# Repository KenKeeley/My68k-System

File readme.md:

# My Motorola 680x0 home built computer system.

My68k System is a home built Motorola 680x0 based small computer project. It is made in the style of vintage computers of the mid
to late 1970's and early 1980's using a mix of classic and modern technologies. The My68k System is made up of multiple PCB's
connected via a common back plane that is loosely based on the VMEBus standard.

The purpose of the My68k System is to entertain through education. It is intended to be used to teach and promote principles of
electronic computer design. It is a solely non-profit educational project and is not intended for any commercial application.
The My68k System and related peripherals would be ideal as a small project to teach basic computer hardware and software
principles.

#### SOFTWARE USED
- [FreeCAD](https://www.freecadweb.org/)
- [KiCad](http://kicad-pcb.org/)
- [KiCad StepUp](https://kicadstepup.sourceforge.io/)

Please report any issues and/or bugs via the "Issues" section on github.
If you have any extra reference material then please submit it via the "Issues" section on github.

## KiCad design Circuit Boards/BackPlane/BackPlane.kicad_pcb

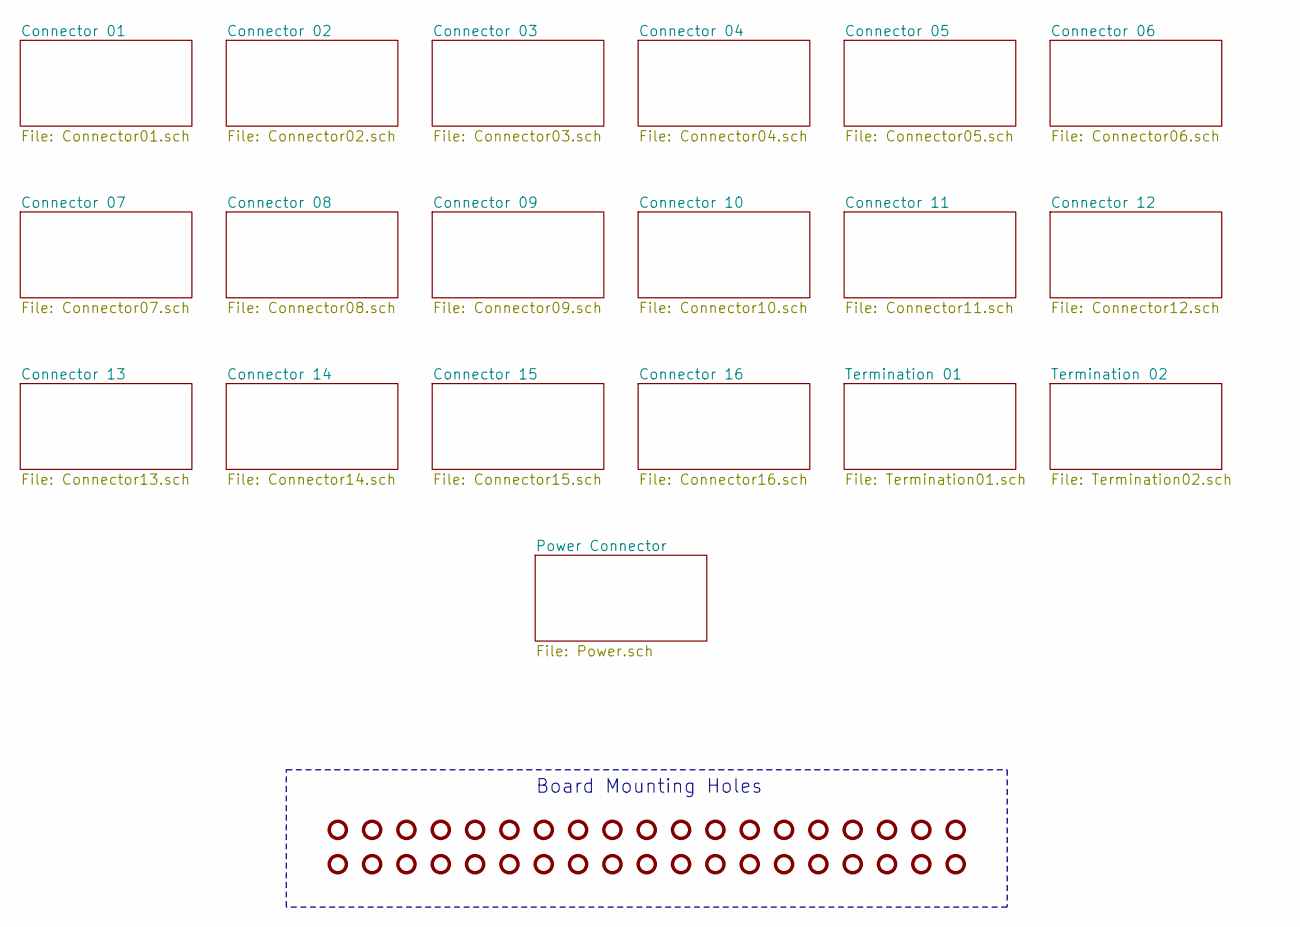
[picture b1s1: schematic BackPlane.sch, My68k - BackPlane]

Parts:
MH1: BackPlane Rails; BackPlane_Rails

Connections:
GND: MH1.1, MH1.2, MH1.3, MH1.4, MH1.5, MH1.6, MH1.7, MH1.8, MH1.9, MH1.10, MH1.11, MH1.12, MH1.13, MH1.14, MH1.15, MH1.16, MH1.17, MH1.18, MH1.19, MH1.20, MH1.21, MH1.22, MH1.23, MH1.24, MH1.25, MH1.26, MH1.27, MH1.28, MH1.29, MH1.30, MH1.31, MH1.32, MH1.33, MH1.34, MH1.35, MH1.36, MH1.37, MH1.38; also elsewhere on the board

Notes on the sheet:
Board Mounting Holes

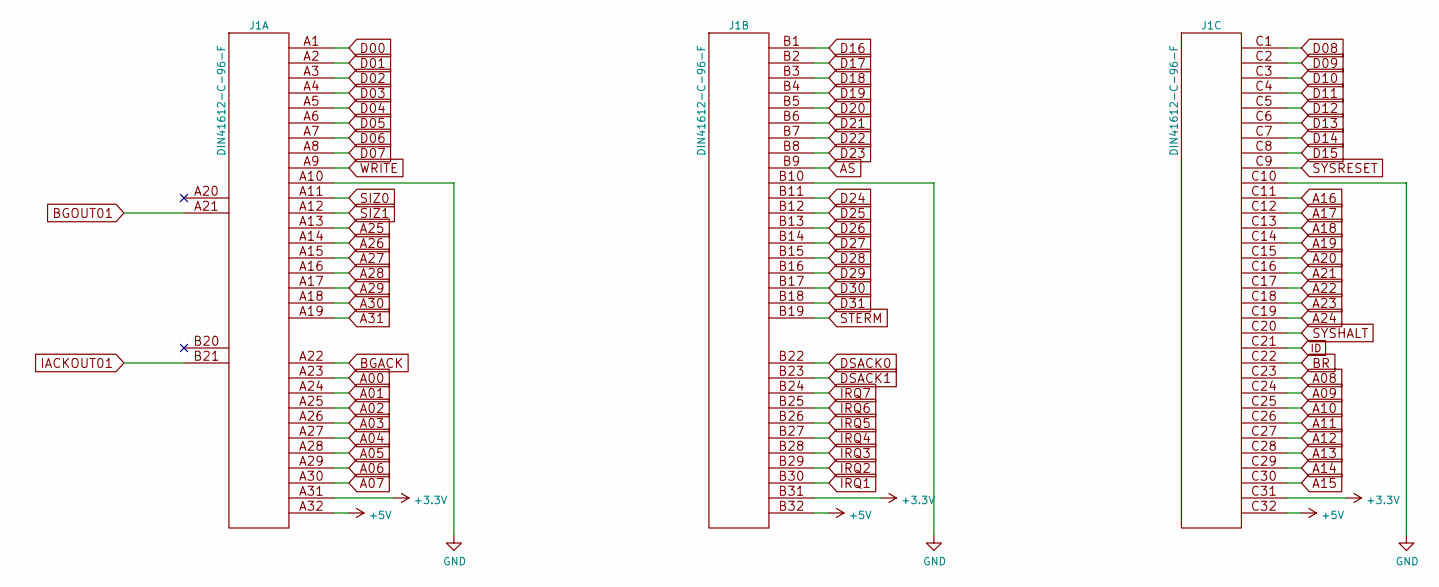
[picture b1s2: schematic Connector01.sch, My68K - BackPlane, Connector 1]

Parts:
J1: DIN41612-C-96-F; Part No. 1656359

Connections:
+3V3: J1.A31, J1.B31, J1.C31; also elsewhere on the board
+5V: J1.A32, J1.B32, J1.C32; also elsewhere on the board
A00: J1.A23; also elsewhere on the board
A01: J1.A24; also elsewhere on the board
A02: J1.A25; also elsewhere on the board
A03: J1.A26; also elsewhere on the board
A04: J1.A27; also elsewhere on the board
A05: J1.A28; also elsewhere on the board
A06: J1.A29; also elsewhere on the board
A07: J1.A30; also elsewhere on the board
A08: J1.C23; also elsewhere on the board
A09: J1.C24; also elsewhere on the board
A10: J1.C25; also elsewhere on the board
A11: J1.C26; also elsewhere on the board
A12: J1.C27; also elsewhere on the board
A13: J1.C28; also elsewhere on the board
A14: J1.C29; also elsewhere on the board
A15: J1.C30; also elsewhere on the board
A16: J1.C11; also elsewhere on the board
A17: J1.C12; also elsewhere on the board
A18: J1.C13; also elsewhere on the board
A19: J1.C14; also elsewhere on the board
A20: J1.C15; also elsewhere on the board
A21: J1.C16; also elsewhere on the board
A22: J1.C17; also elsewhere on the board
A23: J1.C18; also elsewhere on the board
A24: J1.C19; also elsewhere on the board
A25: J1.A13; also elsewhere on the board
A26: J1.A14; also elsewhere on the board
A27: J1.A15; also elsewhere on the board
A28: J1.A16; also elsewhere on the board
A29: J1.A17; also elsewhere on the board
A30: J1.A18; also elsewhere on the board
A31: J1.A19; also elsewhere on the board
AS: J1.B9; also elsewhere on the board
BGACK: J1.A22; also elsewhere on the board
BGOUT01: J1.A21; also elsewhere on the board
BR: J1.C22; also elsewhere on the board
D00: J1.A1; also elsewhere on the board
D01: J1.A2; also elsewhere on the board
D02: J1.A3; also elsewhere on the board
D03: J1.A4; also elsewhere on the board
D04: J1.A5; also elsewhere on the board
D05: J1.A6; also elsewhere on the board
D06: J1.A7; also elsewhere on the board
D07: J1.A8; also elsewhere on the board
D08: J1.C1; also elsewhere on the board
D09: J1.C2; also elsewhere on the board
D10: J1.C3; also elsewhere on the board
D11: J1.C4; also elsewhere on the board
D12: J1.C5; also elsewhere on the board
D13: J1.C6; also elsewhere on the board
D14: J1.C7; also elsewhere on the board
D15: J1.C8; also elsewhere on the board
D16: J1.B1; also elsewhere on the board
D17: J1.B2; also elsewhere on the board
D18: J1.B3; also elsewhere on the board
D19: J1.B4; also elsewhere on the board
D20: J1.B5; also elsewhere on the board
D21: J1.B6; also elsewhere on the board
D22: J1.B7; also elsewhere on the board
D23: J1.B8; also elsewhere on the board
D24: J1.B11; also elsewhere on the board
D25: J1.B12; also elsewhere on the board
D26: J1.B13; also elsewhere on the board
D27: J1.B14; also elsewhere on the board
D28: J1.B15; also elsewhere on the board
D29: J1.B16; also elsewhere on the board
D30: J1.B17; also elsewhere on the board
D31: J1.B18; also elsewhere on the board
DSACK0: J1.B22; also elsewhere on the board
DSACK1: J1.B23; also elsewhere on the board
GND: J1.33 (GND), J1.34 (GND), J1.A10, J1.B10, J1.C10; also elsewhere on the board
IACKOUT01: J1.B21; also elsewhere on the board
ID: J1.C21; also elsewhere on the board
IRQ1: J1.B30; also elsewhere on the board
IRQ2: J1.B29; also elsewhere on the board
IRQ3: J1.B28; also elsewhere on the board
IRQ4: J1.B27; also elsewhere on the board
IRQ5: J1.B26; also elsewhere on the board
IRQ6: J1.B25; also elsewhere on the board
IRQ7: J1.B24; also elsewhere on the board
SIZ0: J1.A11; also elsewhere on the board
SIZ1: J1.A12; also elsewhere on the board
STERM: J1.B19; also elsewhere on the board
SYSHALT: J1.C20; also elsewhere on the board
SYSRESET: J1.C9; also elsewhere on the board
WRITE: J1.A9; also elsewhere on the board

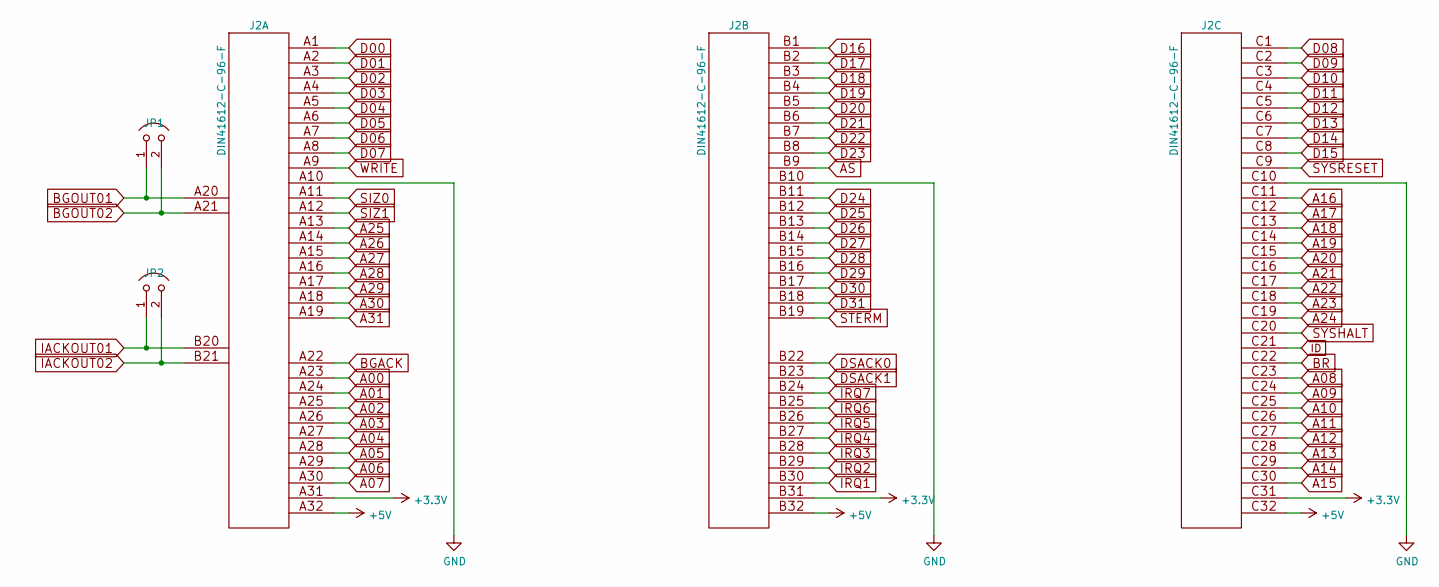
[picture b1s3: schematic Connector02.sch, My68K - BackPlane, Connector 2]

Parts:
J2: DIN41612-C-96-F; Part No. 1656359
JP1, JP2: Jumper; Part No. 1593411

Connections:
+3V3: J2.A31, J2.B31, J2.C31; also elsewhere on the board
+5V: J2.A32, J2.B32, J2.C32; also elsewhere on the board
A00: J2.A23; also elsewhere on the board
A01: J2.A24; also elsewhere on the board
A02: J2.A25; also elsewhere on the board
A03: J2.A26; also elsewhere on the board
A04: J2.A27; also elsewhere on the board
A05: J2.A28; also elsewhere on the board
A06: J2.A29; also elsewhere on the board
A07: J2.A30; also elsewhere on the board
A08: J2.C23; also elsewhere on the board
A09: J2.C24; also elsewhere on the board
A10: J2.C25; also elsewhere on the board
A11: J2.C26; also elsewhere on the board
A12: J2.C27; also elsewhere on the board
A13: J2.C28; also elsewhere on the board
A14: J2.C29; also elsewhere on the board
A15: J2.C30; also elsewhere on the board
A16: J2.C11; also elsewhere on the board
A17: J2.C12; also elsewhere on the board
A18: J2.C13; also elsewhere on the board
A19: J2.C14; also elsewhere on the board
A20: J2.C15; also elsewhere on the board
A21: J2.C16; also elsewhere on the board
A22: J2.C17; also elsewhere on the board
A23: J2.C18; also elsewhere on the board
A24: J2.C19; also elsewhere on the board
A25: J2.A13; also elsewhere on the board
A26: J2.A14; also elsewhere on the board
A27: J2.A15; also elsewhere on the board
A28: J2.A16; also elsewhere on the board
A29: J2.A17; also elsewhere on the board
A30: J2.A18; also elsewhere on the board
A31: J2.A19; also elsewhere on the board
AS: J2.B9; also elsewhere on the board
BGACK: J2.A22; also elsewhere on the board
BGOUT01: J2.A20, JP1.1; also elsewhere on the board
BGOUT02: J2.A21, JP1.2; also elsewhere on the board
BR: J2.C22; also elsewhere on the board
D00: J2.A1; also elsewhere on the board
D01: J2.A2; also elsewhere on the board
D02: J2.A3; also elsewhere on the board
D03: J2.A4; also elsewhere on the board
D04: J2.A5; also elsewhere on the board
D05: J2.A6; also elsewhere on the board
D06: J2.A7; also elsewhere on the board
D07: J2.A8; also elsewhere on the board
D08: J2.C1; also elsewhere on the board
D09: J2.C2; also elsewhere on the board
D10: J2.C3; also elsewhere on the board
D11: J2.C4; also elsewhere on the board
D12: J2.C5; also elsewhere on the board
D13: J2.C6; also elsewhere on the board
D14: J2.C7; also elsewhere on the board
D15: J2.C8; also elsewhere on the board
D16: J2.B1; also elsewhere on the board
D17: J2.B2; also elsewhere on the board
D18: J2.B3; also elsewhere on the board
D19: J2.B4; also elsewhere on the board
D20: J2.B5; also elsewhere on the board
D21: J2.B6; also elsewhere on the board
D22: J2.B7; also elsewhere on the board
D23: J2.B8; also elsewhere on the board
D24: J2.B11; also elsewhere on the board
D25: J2.B12; also elsewhere on the board
D26: J2.B13; also elsewhere on the board
D27: J2.B14; also elsewhere on the board
D28: J2.B15; also elsewhere on the board
D29: J2.B16; also elsewhere on the board
D30: J2.B17; also elsewhere on the board
D31: J2.B18; also elsewhere on the board
DSACK0: J2.B22; also elsewhere on the board
DSACK1: J2.B23; also elsewhere on the board
GND: J2.33 (GND), J2.34 (GND), J2.A10, J2.B10, J2.C10; also elsewhere on the board
IACKOUT01: J2.B20, JP2.1; also elsewhere on the board
IACKOUT02: J2.B21, JP2.2; also elsewhere on the board
ID: J2.C21; also elsewhere on the board
IRQ1: J2.B30; also elsewhere on the board
IRQ2: J2.B29; also elsewhere on the board
IRQ3: J2.B28; also elsewhere on the board
IRQ4: J2.B27; also elsewhere on the board
IRQ5: J2.B26; also elsewhere on the board
IRQ6: J2.B25; also elsewhere on the board
IRQ7: J2.B24; also elsewhere on the board
SIZ0: J2.A11; also elsewhere on the board
SIZ1: J2.A12; also elsewhere on the board
STERM: J2.B19; also elsewhere on the board
SYSHALT: J2.C20; also elsewhere on the board
SYSRESET: J2.C9; also elsewhere on the board
WRITE: J2.A9; also elsewhere on the board

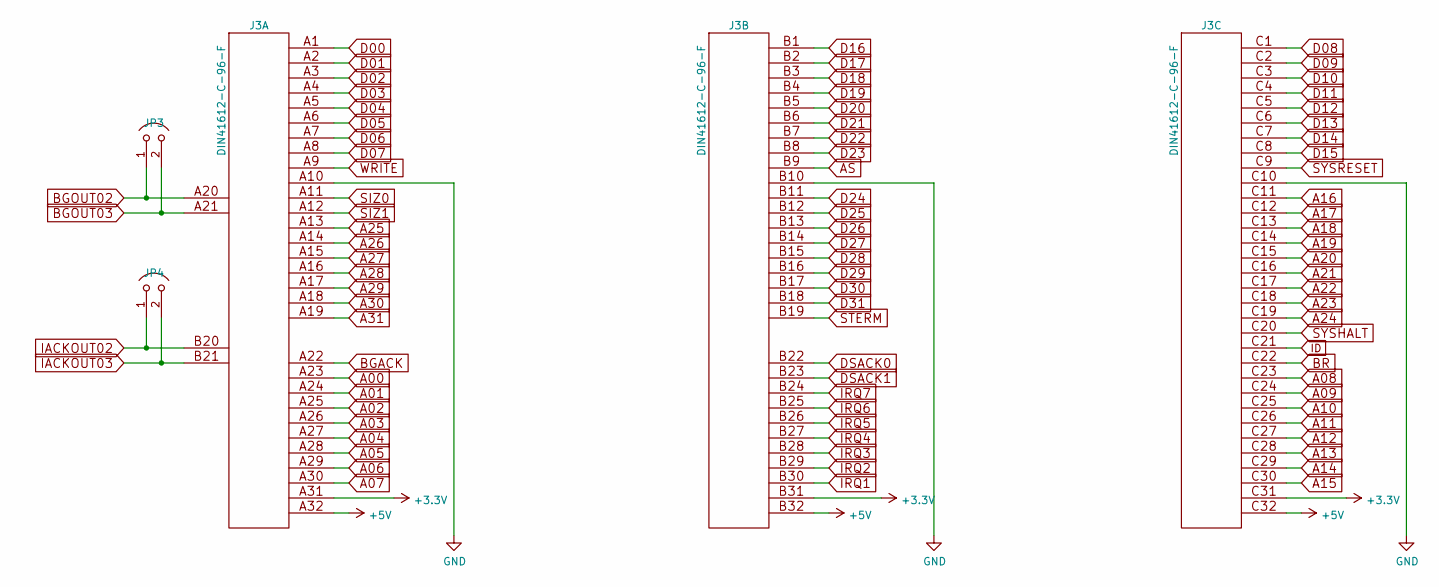
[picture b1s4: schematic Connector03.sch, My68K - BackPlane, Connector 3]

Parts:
J3: DIN41612-C-96-F; Part No. 1656359
JP3, JP4: Jumper; Part No. 1593411

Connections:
+3V3: J3.A31, J3.B31, J3.C31; also elsewhere on the board
+5V: J3.A32, J3.B32, J3.C32; also elsewhere on the board
A00: J3.A23; also elsewhere on the board
A01: J3.A24; also elsewhere on the board
A02: J3.A25; also elsewhere on the board
A03: J3.A26; also elsewhere on the board
A04: J3.A27; also elsewhere on the board
A05: J3.A28; also elsewhere on the board
A06: J3.A29; also elsewhere on the board
A07: J3.A30; also elsewhere on the board
A08: J3.C23; also elsewhere on the board
A09: J3.C24; also elsewhere on the board
A10: J3.C25; also elsewhere on the board
A11: J3.C26; also elsewhere on the board
A12: J3.C27; also elsewhere on the board
A13: J3.C28; also elsewhere on the board
A14: J3.C29; also elsewhere on the board
A15: J3.C30; also elsewhere on the board
A16: J3.C11; also elsewhere on the board
A17: J3.C12; also elsewhere on the board
A18: J3.C13; also elsewhere on the board
A19: J3.C14; also elsewhere on the board
A20: J3.C15; also elsewhere on the board
A21: J3.C16; also elsewhere on the board
A22: J3.C17; also elsewhere on the board
A23: J3.C18; also elsewhere on the board
A24: J3.C19; also elsewhere on the board
A25: J3.A13; also elsewhere on the board
A26: J3.A14; also elsewhere on the board
A27: J3.A15; also elsewhere on the board
A28: J3.A16; also elsewhere on the board
A29: J3.A17; also elsewhere on the board
A30: J3.A18; also elsewhere on the board
A31: J3.A19; also elsewhere on the board
AS: J3.B9; also elsewhere on the board
BGACK: J3.A22; also elsewhere on the board
BGOUT02: J3.A20, JP3.1; also elsewhere on the board
BGOUT03: J3.A21, JP3.2; also elsewhere on the board
BR: J3.C22; also elsewhere on the board
D00: J3.A1; also elsewhere on the board
D01: J3.A2; also elsewhere on the board
D02: J3.A3; also elsewhere on the board
D03: J3.A4; also elsewhere on the board
D04: J3.A5; also elsewhere on the board
D05: J3.A6; also elsewhere on the board
D06: J3.A7; also elsewhere on the board
D07: J3.A8; also elsewhere on the board
D08: J3.C1; also elsewhere on the board
D09: J3.C2; also elsewhere on the board
D10: J3.C3; also elsewhere on the board
D11: J3.C4; also elsewhere on the board
D12: J3.C5; also elsewhere on the board
D13: J3.C6; also elsewhere on the board
D14: J3.C7; also elsewhere on the board
D15: J3.C8; also elsewhere on the board
D16: J3.B1; also elsewhere on the board
D17: J3.B2; also elsewhere on the board
D18: J3.B3; also elsewhere on the board
D19: J3.B4; also elsewhere on the board
D20: J3.B5; also elsewhere on the board
D21: J3.B6; also elsewhere on the board
D22: J3.B7; also elsewhere on the board
D23: J3.B8; also elsewhere on the board
D24: J3.B11; also elsewhere on the board
D25: J3.B12; also elsewhere on the board
D26: J3.B13; also elsewhere on the board
D27: J3.B14; also elsewhere on the board
D28: J3.B15; also elsewhere on the board
D29: J3.B16; also elsewhere on the board
D30: J3.B17; also elsewhere on the board
D31: J3.B18; also elsewhere on the board
DSACK0: J3.B22; also elsewhere on the board
DSACK1: J3.B23; also elsewhere on the board
GND: J3.33 (GND), J3.34 (GND), J3.A10, J3.B10, J3.C10; also elsewhere on the board
IACKOUT02: J3.B20, JP4.1; also elsewhere on the board
IACKOUT03: J3.B21, JP4.2; also elsewhere on the board
ID: J3.C21; also elsewhere on the board
IRQ1: J3.B30; also elsewhere on the board
IRQ2: J3.B29; also elsewhere on the board
IRQ3: J3.B28; also elsewhere on the board
IRQ4: J3.B27; also elsewhere on the board
IRQ5: J3.B26; also elsewhere on the board
IRQ6: J3.B25; also elsewhere on the board
IRQ7: J3.B24; also elsewhere on the board
SIZ0: J3.A11; also elsewhere on the board
SIZ1: J3.A12; also elsewhere on the board
STERM: J3.B19; also elsewhere on the board
SYSHALT: J3.C20; also elsewhere on the board
SYSRESET: J3.C9; also elsewhere on the board
WRITE: J3.A9; also elsewhere on the board

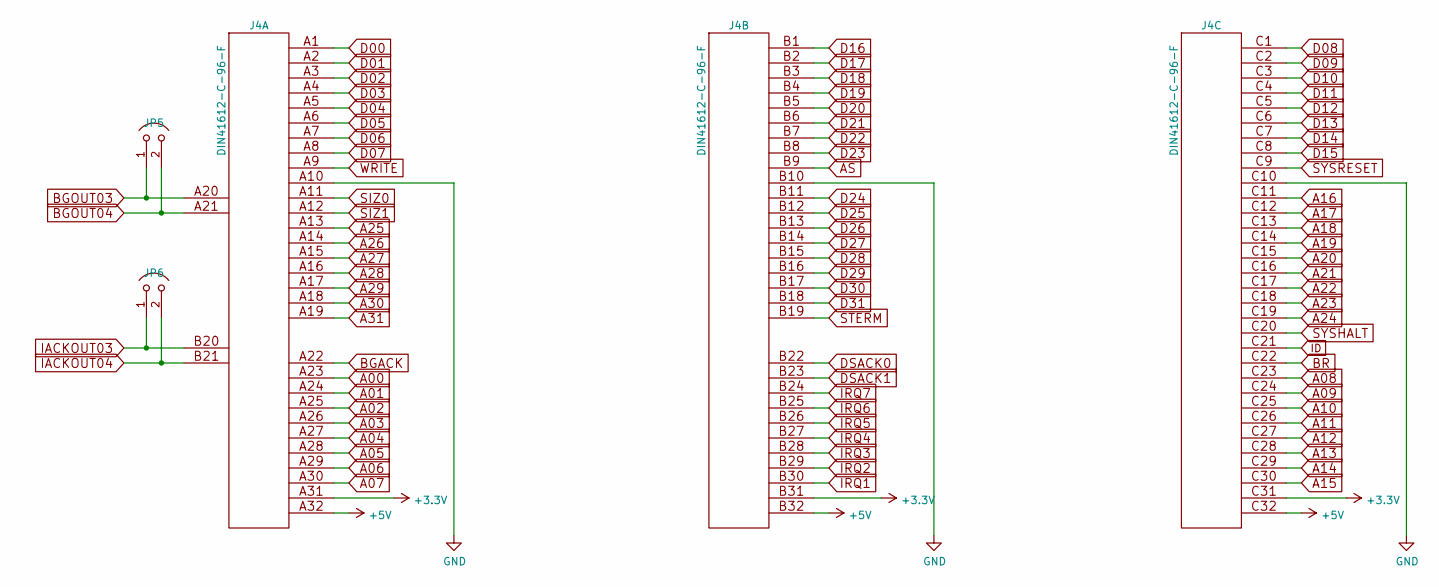
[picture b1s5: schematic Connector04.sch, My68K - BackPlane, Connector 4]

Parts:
J4: DIN41612-C-96-F; Part No. 1656359
JP5, JP6: Jumper; Part No. 1593411

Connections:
+3V3: J4.A31, J4.B31, J4.C31; also elsewhere on the board
+5V: J4.A32, J4.B32, J4.C32; also elsewhere on the board
A00: J4.A23; also elsewhere on the board
A01: J4.A24; also elsewhere on the board
A02: J4.A25; also elsewhere on the board
A03: J4.A26; also elsewhere on the board
A04: J4.A27; also elsewhere on the board
A05: J4.A28; also elsewhere on the board
A06: J4.A29; also elsewhere on the board
A07: J4.A30; also elsewhere on the board
A08: J4.C23; also elsewhere on the board
A09: J4.C24; also elsewhere on the board
A10: J4.C25; also elsewhere on the board
A11: J4.C26; also elsewhere on the board
A12: J4.C27; also elsewhere on the board
A13: J4.C28; also elsewhere on the board
A14: J4.C29; also elsewhere on the board
A15: J4.C30; also elsewhere on the board
A16: J4.C11; also elsewhere on the board
A17: J4.C12; also elsewhere on the board
A18: J4.C13; also elsewhere on the board
A19: J4.C14; also elsewhere on the board
A20: J4.C15; also elsewhere on the board
A21: J4.C16; also elsewhere on the board
A22: J4.C17; also elsewhere on the board
A23: J4.C18; also elsewhere on the board
A24: J4.C19; also elsewhere on the board
A25: J4.A13; also elsewhere on the board
A26: J4.A14; also elsewhere on the board
A27: J4.A15; also elsewhere on the board
A28: J4.A16; also elsewhere on the board
A29: J4.A17; also elsewhere on the board
A30: J4.A18; also elsewhere on the board
A31: J4.A19; also elsewhere on the board
AS: J4.B9; also elsewhere on the board
BGACK: J4.A22; also elsewhere on the board
BGOUT03: J4.A20, JP5.1; also elsewhere on the board
BGOUT04: J4.A21, JP5.2; also elsewhere on the board
BR: J4.C22; also elsewhere on the board
D00: J4.A1; also elsewhere on the board
D01: J4.A2; also elsewhere on the board
D02: J4.A3; also elsewhere on the board
D03: J4.A4; also elsewhere on the board
D04: J4.A5; also elsewhere on the board
D05: J4.A6; also elsewhere on the board
D06: J4.A7; also elsewhere on the board
D07: J4.A8; also elsewhere on the board
D08: J4.C1; also elsewhere on the board
D09: J4.C2; also elsewhere on the board
D10: J4.C3; also elsewhere on the board
D11: J4.C4; also elsewhere on the board
D12: J4.C5; also elsewhere on the board
D13: J4.C6; also elsewhere on the board
D14: J4.C7; also elsewhere on the board
D15: J4.C8; also elsewhere on the board
D16: J4.B1; also elsewhere on the board
D17: J4.B2; also elsewhere on the board
D18: J4.B3; also elsewhere on the board
D19: J4.B4; also elsewhere on the board
D20: J4.B5; also elsewhere on the board
D21: J4.B6; also elsewhere on the board
D22: J4.B7; also elsewhere on the board
D23: J4.B8; also elsewhere on the board
D24: J4.B11; also elsewhere on the board
D25: J4.B12; also elsewhere on the board
D26: J4.B13; also elsewhere on the board
D27: J4.B14; also elsewhere on the board
D28: J4.B15; also elsewhere on the board
D29: J4.B16; also elsewhere on the board
D30: J4.B17; also elsewhere on the board
D31: J4.B18; also elsewhere on the board
DSACK0: J4.B22; also elsewhere on the board
DSACK1: J4.B23; also elsewhere on the board
GND: J4.33 (GND), J4.34 (GND), J4.A10, J4.B10, J4.C10; also elsewhere on the board
IACKOUT03: J4.B20, JP6.1; also elsewhere on the board
IACKOUT04: J4.B21, JP6.2; also elsewhere on the board
ID: J4.C21; also elsewhere on the board
IRQ1: J4.B30; also elsewhere on the board
IRQ2: J4.B29; also elsewhere on the board
IRQ3: J4.B28; also elsewhere on the board
IRQ4: J4.B27; also elsewhere on the board
IRQ5: J4.B26; also elsewhere on the board
IRQ6: J4.B25; also elsewhere on the board
IRQ7: J4.B24; also elsewhere on the board
SIZ0: J4.A11; also elsewhere on the board
SIZ1: J4.A12; also elsewhere on the board
STERM: J4.B19; also elsewhere on the board
SYSHALT: J4.C20; also elsewhere on the board
SYSRESET: J4.C9; also elsewhere on the board
WRITE: J4.A9; also elsewhere on the board

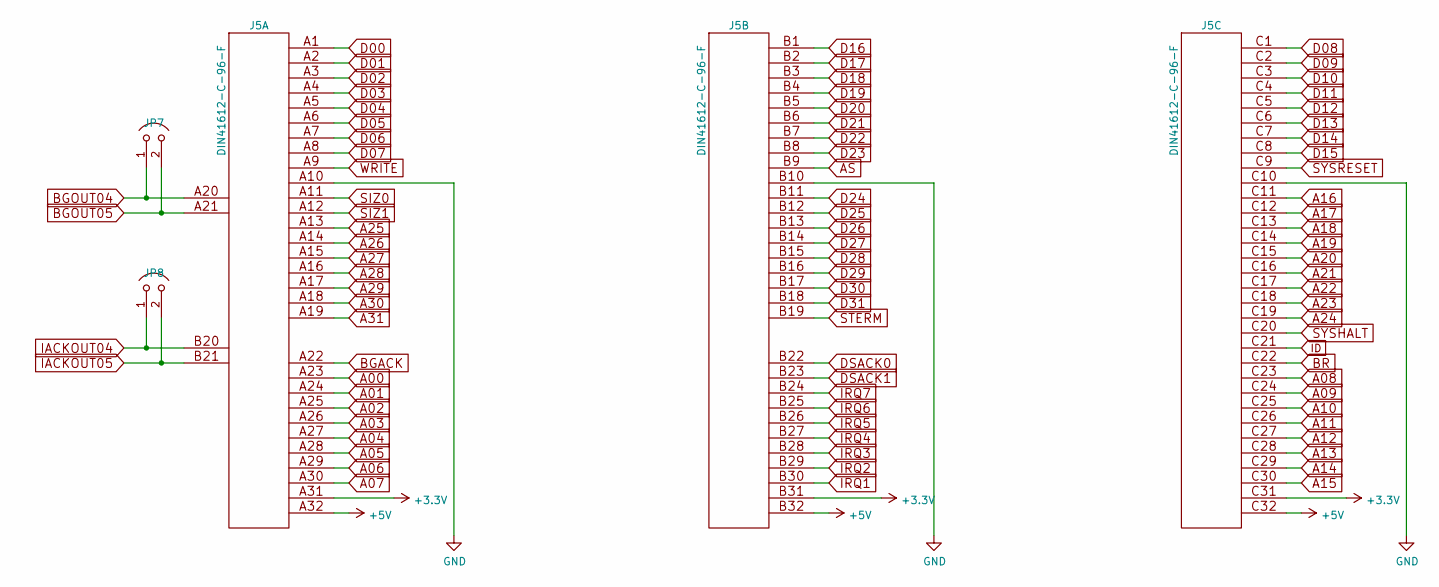
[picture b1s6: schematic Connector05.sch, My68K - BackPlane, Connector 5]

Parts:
J5: DIN41612-C-96-F; Part No. 1656359
JP7, JP8: Jumper; Part No. 1593411

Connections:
+3V3: J5.A31, J5.B31, J5.C31; also elsewhere on the board
+5V: J5.A32, J5.B32, J5.C32; also elsewhere on the board
A00: J5.A23; also elsewhere on the board
A01: J5.A24; also elsewhere on the board
A02: J5.A25; also elsewhere on the board
A03: J5.A26; also elsewhere on the board
A04: J5.A27; also elsewhere on the board
A05: J5.A28; also elsewhere on the board
A06: J5.A29; also elsewhere on the board
A07: J5.A30; also elsewhere on the board
A08: J5.C23; also elsewhere on the board
A09: J5.C24; also elsewhere on the board
A10: J5.C25; also elsewhere on the board
A11: J5.C26; also elsewhere on the board
A12: J5.C27; also elsewhere on the board
A13: J5.C28; also elsewhere on the board
A14: J5.C29; also elsewhere on the board
A15: J5.C30; also elsewhere on the board
A16: J5.C11; also elsewhere on the board
A17: J5.C12; also elsewhere on the board
A18: J5.C13; also elsewhere on the board
A19: J5.C14; also elsewhere on the board
A20: J5.C15; also elsewhere on the board
A21: J5.C16; also elsewhere on the board
A22: J5.C17; also elsewhere on the board
A23: J5.C18; also elsewhere on the board
A24: J5.C19; also elsewhere on the board
A25: J5.A13; also elsewhere on the board
A26: J5.A14; also elsewhere on the board
A27: J5.A15; also elsewhere on the board
A28: J5.A16; also elsewhere on the board
A29: J5.A17; also elsewhere on the board
A30: J5.A18; also elsewhere on the board
A31: J5.A19; also elsewhere on the board
AS: J5.B9; also elsewhere on the board
BGACK: J5.A22; also elsewhere on the board
BGOUT04: J5.A20, JP7.1; also elsewhere on the board
BGOUT05: J5.A21, JP7.2; also elsewhere on the board
BR: J5.C22; also elsewhere on the board
D00: J5.A1; also elsewhere on the board
D01: J5.A2; also elsewhere on the board
D02: J5.A3; also elsewhere on the board
D03: J5.A4; also elsewhere on the board
D04: J5.A5; also elsewhere on the board
D05: J5.A6; also elsewhere on the board
D06: J5.A7; also elsewhere on the board
D07: J5.A8; also elsewhere on the board
D08: J5.C1; also elsewhere on the board
D09: J5.C2; also elsewhere on the board
D10: J5.C3; also elsewhere on the board
D11: J5.C4; also elsewhere on the board
D12: J5.C5; also elsewhere on the board
D13: J5.C6; also elsewhere on the board
D14: J5.C7; also elsewhere on the board
D15: J5.C8; also elsewhere on the board
D16: J5.B1; also elsewhere on the board
D17: J5.B2; also elsewhere on the board
D18: J5.B3; also elsewhere on the board
D19: J5.B4; also elsewhere on the board
D20: J5.B5; also elsewhere on the board
D21: J5.B6; also elsewhere on the board
D22: J5.B7; also elsewhere on the board
D23: J5.B8; also elsewhere on the board
D24: J5.B11; also elsewhere on the board
D25: J5.B12; also elsewhere on the board
D26: J5.B13; also elsewhere on the board
D27: J5.B14; also elsewhere on the board
D28: J5.B15; also elsewhere on the board
D29: J5.B16; also elsewhere on the board
D30: J5.B17; also elsewhere on the board
D31: J5.B18; also elsewhere on the board
DSACK0: J5.B22; also elsewhere on the board
DSACK1: J5.B23; also elsewhere on the board
GND: J5.33 (GND), J5.34 (GND), J5.A10, J5.B10, J5.C10; also elsewhere on the board
IACKOUT04: J5.B20, JP8.1; also elsewhere on the board
IACKOUT05: J5.B21, JP8.2; also elsewhere on the board
ID: J5.C21; also elsewhere on the board
IRQ1: J5.B30; also elsewhere on the board
IRQ2: J5.B29; also elsewhere on the board
IRQ3: J5.B28; also elsewhere on the board
IRQ4: J5.B27; also elsewhere on the board
IRQ5: J5.B26; also elsewhere on the board
IRQ6: J5.B25; also elsewhere on the board
IRQ7: J5.B24; also elsewhere on the board
SIZ0: J5.A11; also elsewhere on the board
SIZ1: J5.A12; also elsewhere on the board
STERM: J5.B19; also elsewhere on the board
SYSHALT: J5.C20; also elsewhere on the board
SYSRESET: J5.C9; also elsewhere on the board
WRITE: J5.A9; also elsewhere on the board

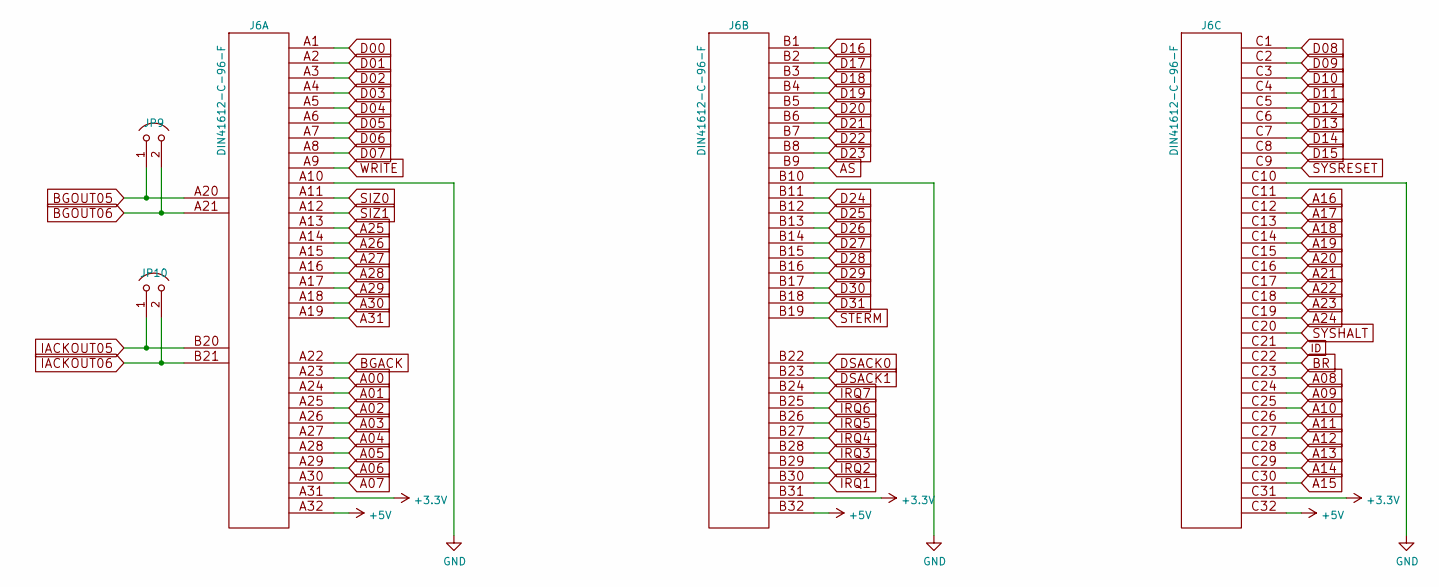
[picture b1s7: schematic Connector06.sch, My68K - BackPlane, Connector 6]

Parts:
J6: DIN41612-C-96-F; Part No. 1656359
JP9, JP10: Jumper; Part No. 1593411

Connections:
+3V3: J6.A31, J6.B31, J6.C31; also elsewhere on the board
+5V: J6.A32, J6.B32, J6.C32; also elsewhere on the board
A00: J6.A23; also elsewhere on the board
A01: J6.A24; also elsewhere on the board
A02: J6.A25; also elsewhere on the board
A03: J6.A26; also elsewhere on the board
A04: J6.A27; also elsewhere on the board
A05: J6.A28; also elsewhere on the board
A06: J6.A29; also elsewhere on the board
A07: J6.A30; also elsewhere on the board
A08: J6.C23; also elsewhere on the board
A09: J6.C24; also elsewhere on the board
A10: J6.C25; also elsewhere on the board
A11: J6.C26; also elsewhere on the board
A12: J6.C27; also elsewhere on the board
A13: J6.C28; also elsewhere on the board
A14: J6.C29; also elsewhere on the board
A15: J6.C30; also elsewhere on the board
A16: J6.C11; also elsewhere on the board
A17: J6.C12; also elsewhere on the board
A18: J6.C13; also elsewhere on the board
A19: J6.C14; also elsewhere on the board
A20: J6.C15; also elsewhere on the board
A21: J6.C16; also elsewhere on the board
A22: J6.C17; also elsewhere on the board
A23: J6.C18; also elsewhere on the board
A24: J6.C19; also elsewhere on the board
A25: J6.A13; also elsewhere on the board
A26: J6.A14; also elsewhere on the board
A27: J6.A15; also elsewhere on the board
A28: J6.A16; also elsewhere on the board
A29: J6.A17; also elsewhere on the board
A30: J6.A18; also elsewhere on the board
A31: J6.A19; also elsewhere on the board
AS: J6.B9; also elsewhere on the board
BGACK: J6.A22; also elsewhere on the board
BGOUT05: J6.A20, JP9.1; also elsewhere on the board
BGOUT06: J6.A21, JP9.2; also elsewhere on the board
BR: J6.C22; also elsewhere on the board
D00: J6.A1; also elsewhere on the board
D01: J6.A2; also elsewhere on the board
D02: J6.A3; also elsewhere on the board
D03: J6.A4; also elsewhere on the board
D04: J6.A5; also elsewhere on the board
D05: J6.A6; also elsewhere on the board
D06: J6.A7; also elsewhere on the board
D07: J6.A8; also elsewhere on the board
D08: J6.C1; also elsewhere on the board
D09: J6.C2; also elsewhere on the board
D10: J6.C3; also elsewhere on the board
D11: J6.C4; also elsewhere on the board
D12: J6.C5; also elsewhere on the board
D13: J6.C6; also elsewhere on the board
D14: J6.C7; also elsewhere on the board
D15: J6.C8; also elsewhere on the board
D16: J6.B1; also elsewhere on the board
D17: J6.B2; also elsewhere on the board
D18: J6.B3; also elsewhere on the board
D19: J6.B4; also elsewhere on the board
D20: J6.B5; also elsewhere on the board
D21: J6.B6; also elsewhere on the board
D22: J6.B7; also elsewhere on the board
D23: J6.B8; also elsewhere on the board
D24: J6.B11; also elsewhere on the board
D25: J6.B12; also elsewhere on the board
D26: J6.B13; also elsewhere on the board
D27: J6.B14; also elsewhere on the board
D28: J6.B15; also elsewhere on the board
D29: J6.B16; also elsewhere on the board
D30: J6.B17; also elsewhere on the board
D31: J6.B18; also elsewhere on the board
DSACK0: J6.B22; also elsewhere on the board
DSACK1: J6.B23; also elsewhere on the board
GND: J6.33 (GND), J6.34 (GND), J6.A10, J6.B10, J6.C10; also elsewhere on the board
IACKOUT05: J6.B20, JP10.1; also elsewhere on the board
IACKOUT06: J6.B21, JP10.2; also elsewhere on the board
ID: J6.C21; also elsewhere on the board
IRQ1: J6.B30; also elsewhere on the board
IRQ2: J6.B29; also elsewhere on the board
IRQ3: J6.B28; also elsewhere on the board
IRQ4: J6.B27; also elsewhere on the board
IRQ5: J6.B26; also elsewhere on the board
IRQ6: J6.B25; also elsewhere on the board
IRQ7: J6.B24; also elsewhere on the board
SIZ0: J6.A11; also elsewhere on the board
SIZ1: J6.A12; also elsewhere on the board
STERM: J6.B19; also elsewhere on the board
SYSHALT: J6.C20; also elsewhere on the board
SYSRESET: J6.C9; also elsewhere on the board
WRITE: J6.A9; also elsewhere on the board
